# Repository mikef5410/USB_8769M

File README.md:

## USB_8769M 

USB control of Keysight 50GHz SP6T.

Related projects: [my USB Dual SPDT project](https://github.com/mikef5410/USB_SPDT)  and  [the software for these projects](https://github.com/mikef5410/USB_Attenuator_Switch_Stacklight)

# Project setup

The software is included here as a git submodule. After cloning, do a
`git submodule init` followed by `git submodule update --recursive`

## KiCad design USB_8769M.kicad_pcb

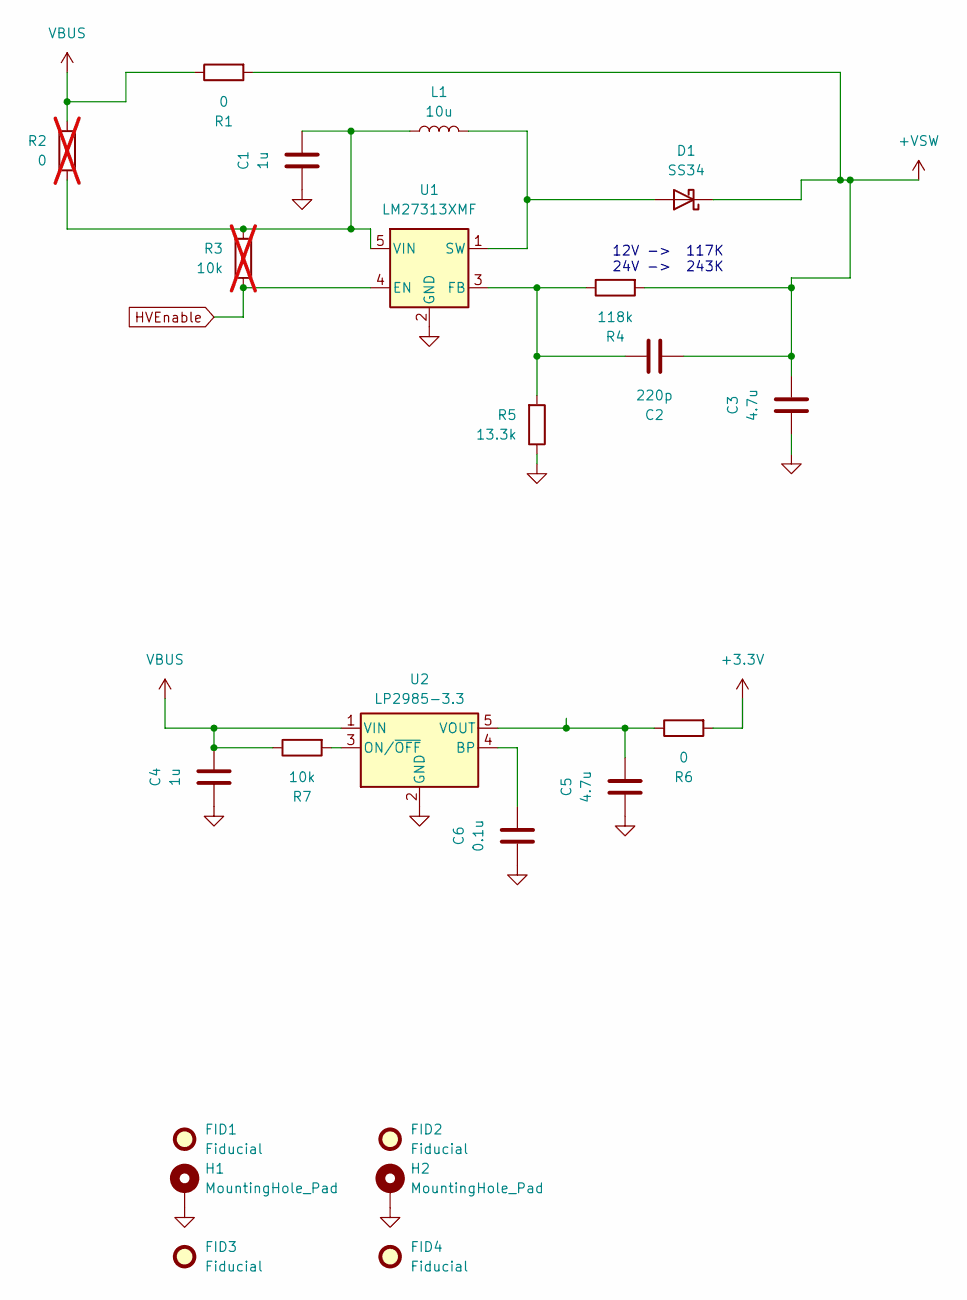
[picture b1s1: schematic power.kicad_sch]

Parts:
C1, C4: 1u; C_0603_1608Metric_Pad1.08x0.95mm_HandSolder; LCSC C15849
C2: 220p; C_0402_1005Metric_Pad0.74x0.62mm_HandSolder; LCSC C1603
C3: 4.7u; C_0805_2012Metric_Pad1.18x1.45mm_HandSolder; LCSC C1779
C5: 4.7u; C_0402_1005Metric_Pad0.74x0.62mm_HandSolder; LCSC C106859
C6: 0.1u; C_0402_1005Metric_Pad0.74x0.62mm_HandSolder; LCSC C5142567
D1: SS34; D_SMA; LCSC C8678
FID1, FID2, FID3, FID4: Fiducial; Fiducial_1mm_Mask3mm
H1, H2: MountingHole_Pad; MountingHole_3.2mm_M3_DIN965_Pad_TopBottom
L1: 10u; L_Changjiang_FNR4030S; LCSC C167879
R1, R6: 0; R_0402_1005Metric_Pad0.72x0.64mm_HandSolder; LCSC C17168
R2: 0; R_0402_1005Metric_Pad0.72x0.64mm_HandSolder; LCSC C17168; not fitted
R3: 10k; R_0402_1005Metric_Pad0.72x0.64mm_HandSolder; LCSC C25744; not fitted
R4: 118k; R_0402_1005Metric_Pad0.72x0.64mm_HandSolder; LCSC C25748
R5: 13.3k; R_0402_1005Metric_Pad0.72x0.64mm_HandSolder; LCSC C122547
R7: 10k; R_0402_1005Metric_Pad0.72x0.64mm_HandSolder; LCSC C25744
U1: LM27313XMF; SOT-23-5; LCSC C341750
U2: LP2985-3.3; SOT-23-5; LCSC C109382

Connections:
+3.3V: R6.2; also elsewhere on the board
+VSW: C2.1, C3.2, D1.1 (K), R1.2, R4.2; also elsewhere on the board
GND: C1.1, C3.1, C4.1, C5.1, C6.1, H1.1, H2.1, R5.1, U1.2 (GND), U2.2 (GND); also elsewhere on the board
HVEnable: R3.1, U1.4 (EN); also elsewhere on the board
unnamed: D1.2 (A), L1.2, U1.1 (SW)
unnamed: C2.2, R4.1, R5.2, U1.3 (FB)
unnamed: C1.2, L1.1, R2.1, R3.2, U1.5 (VIN)
unnamed: C6.2, U2.4 (BP)
unnamed: R7.2, U2.3 (ON/~OFF)
unnamed: C5.2, R6.1, U2.5 (VOUT)
VBUS: C4.2, R1.1, R2.2, R7.1, U2.1 (VIN); also elsewhere on the board

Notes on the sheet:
12V -> 117K 24V -> 243K

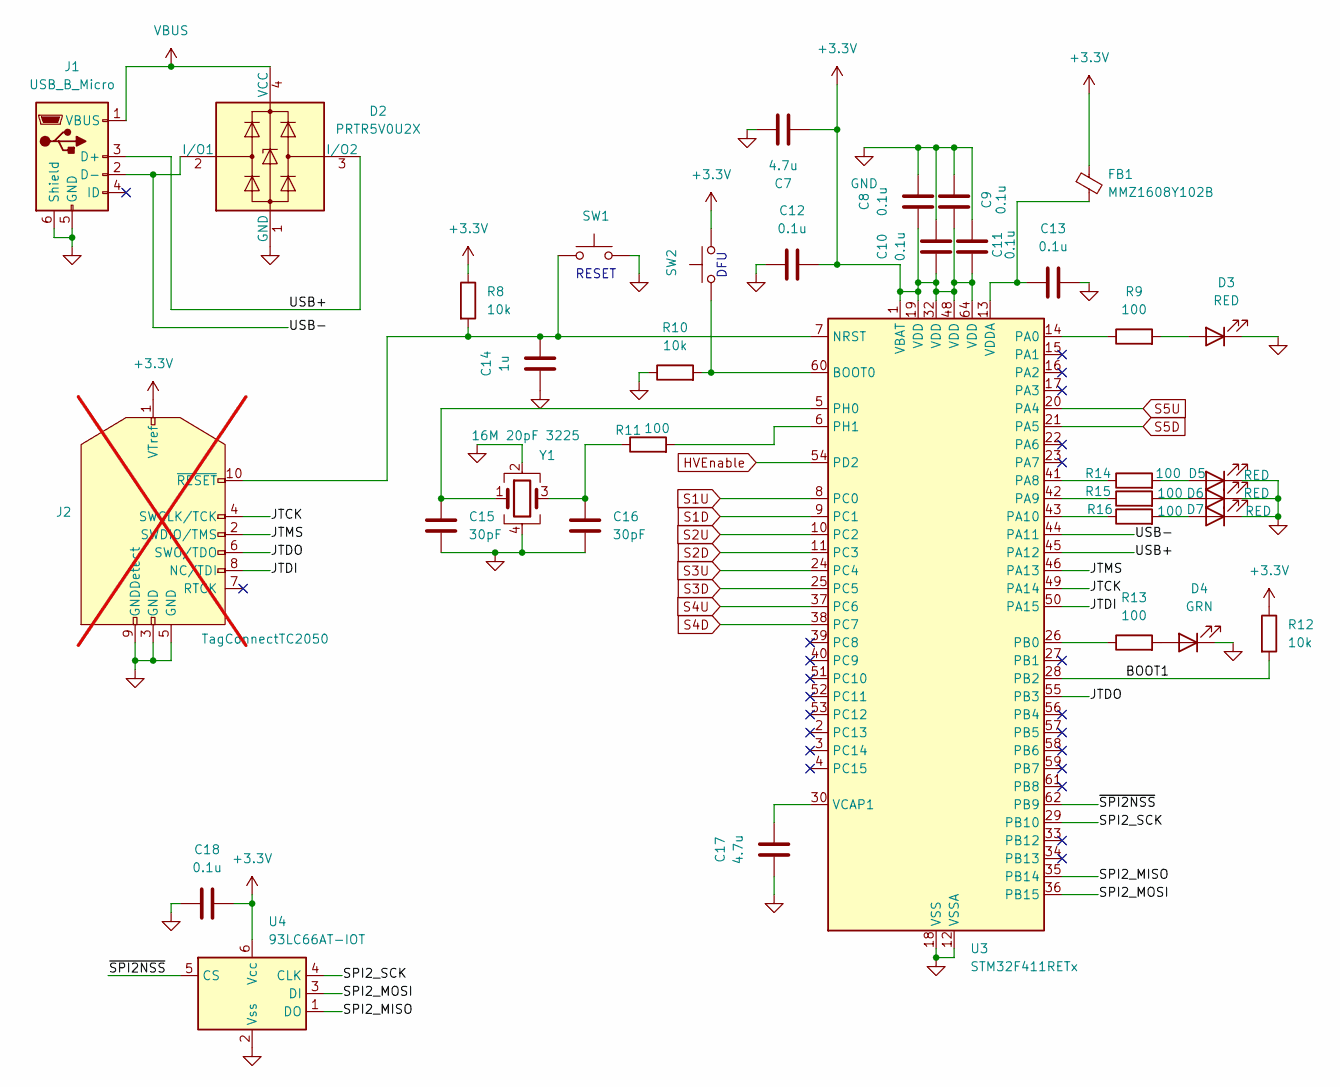
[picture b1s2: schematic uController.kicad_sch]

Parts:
C7, C17: 4.7u; C_0402_1005Metric_Pad0.74x0.62mm_HandSolder; LCSC C106859
C8, C9, C10, C11, C12, C13, C18: 0.1u; C_0402_1005Metric_Pad0.74x0.62mm_HandSolder; LCSC C5142567
C14: 1u; C_0603_1608Metric_Pad1.08x0.95mm_HandSolder; LCSC C15849
C15, C16: 30pF; C_0402_1005Metric_Pad0.74x0.62mm_HandSolder; LCSC C1658
D2: PRTR5V0U2X; SOT-143; LCSC C2827688
D3, D5, D6, D7: RED; LED_0603_1608Metric_Pad1.05x0.95mm_HandSolder; LCSC C84263
D4: GRN; LED_0603_1608Metric_Pad1.05x0.95mm_HandSolder; LCSC C434423
FB1: MMZ1608Y102B; C_0603_1608Metric_Pad1.08x0.95mm_HandSolder; LCSC C114771
J1: USB_B_Micro; USB_Micro-B_Amphenol_10118193-0001LF_Horizontal; LCSC C132562
J2: TagConnectTC2050; Tag-Connect_TC2050-IDC-FP_2x05_P1.27mm_Vertical; not fitted
R8, R10, R12: 10k; R_0402_1005Metric_Pad0.72x0.64mm_HandSolder; LCSC C25744
R9, R11, R13, R14, R15, R16: 100; R_0402_1005Metric_Pad0.72x0.64mm_HandSolder; LCSC C25076
SW1, SW2: SW_Push; SW_Tactile_SPST_NO_Straight_CK_PTS636Sx25SMTRLFS; LCSC C2800965
U3: STM32F411RETx; LQFP-64_10x10mm_P0.5mm; LCSC C94355
U4: 93LC66AT-IOT; SOT-23-6; LCSC C511344
Y1: 16M 20pF 3225; Crystal_SMD_3225-4Pin_3.2x2.5mm_HandSoldering; MPN 7U16000E20UCG; LCSC C524727

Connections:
+3.3V: C7.1, C8.1, C9.2, C10.1, C11.1, C12.2, C18.2, FB1.1, J2.1 (VTref), R8.1, R12.1, SW2.2, U3.1 (VBAT), U3.19 (VDD), U3.32 (VDD), U3.48 (VDD), U3.64 (VDD), U4.6 (Vcc); also elsewhere on the board
/uController/BOOT1: R12.2, U3.28 (PB2)
/uController/JTCK: J2.4 (SWCLK/TCK), U3.49 (PA14)
/uController/JTDI: J2.8 (NC/TDI), U3.50 (PA15)
/uController/JTDO: J2.6 (SWO/TDO), U3.55 (PB3)
/uController/JTMS: J2.2 (SWDIO/TMS), U3.46 (PA13)
/uController/SPI2_MISO: U3.35 (PB14), U4.1 (DO)
/uController/SPI2_MOSI: U3.36 (PB15), U4.3 (DI)
/uController/SPI2_SCK: U3.29 (PB10), U4.4 (CLK)
/uController/USB+: D2.3 (I/O2), J1.3 (D+), U3.45 (PA12)
/uController/USB-: D2.2 (I/O1), J1.2 (D-), U3.44 (PA11)
/uController/~SPI2NSS: U3.62 (PB9), U4.5 (CS)
GND: C7.2, C8.2, C9.1, C10.2, C11.2, C12.1, C13.2, C14.1, C15.2, C16.2, C17.1, C18.1, D2.1 (GND), D3.1 (K), D4.1 (K), D5.1 (K), D6.1 (K), D7.1 (K), J1.5 (GND), J1.6 (Shield), J2.3 (GND), J2.5 (GND), J2.9 (GNDDetect), R10.1, SW1.2, U3.12 (VSSA), U3.18 (VSS), U3.31 (VSS), U3.47 (VSS), U3.63 (VSS), U4.2 (Vss), Y1.2, Y1.4; also elsewhere on the board
HVEnable: U3.54 (PD2); also elsewhere on the board
unnamed: C16.1, R11.1, Y1.3
unnamed: D3.2 (A), R9.2
unnamed: D4.2 (A), R13.2
unnamed: D5.2 (A), R14.2
unnamed: D6.2 (A), R15.2
unnamed: D7.2 (A), R16.2
unnamed: C14.2, J2.10 (~RESET), R8.2, SW1.1, U3.7 (NRST)
unnamed: R10.2, SW2.1, U3.60 (BOOT0)
unnamed: R9.1, U3.14 (PA0)
unnamed: R14.1, U3.41 (PA8)
unnamed: R15.1, U3.42 (PA9)
unnamed: R16.1, U3.43 (PA10)
unnamed: R13.1, U3.26 (PB0)
unnamed: C15.1, U3.5 (PH0), Y1.1
unnamed: R11.2, U3.6 (PH1)
unnamed: C17.2, U3.30 (VCAP1)
unnamed: C13.1, FB1.2, U3.13 (VDDA)
S1D: U3.9 (PC1); also elsewhere on the board
S1U: U3.8 (PC0); also elsewhere on the board
S2D: U3.11 (PC3); also elsewhere on the board
S2U: U3.10 (PC2); also elsewhere on the board
S3D: U3.25 (PC5); also elsewhere on the board
S3U: U3.24 (PC4); also elsewhere on the board
S4D: U3.38 (PC7); also elsewhere on the board
S4U: U3.37 (PC6); also elsewhere on the board
S5D: U3.21 (PA5); also elsewhere on the board
S5U: U3.20 (PA4); also elsewhere on the board
VBUS: D2.4 (VCC), J1.1 (VBUS); also elsewhere on the board

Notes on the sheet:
RESET
DFU

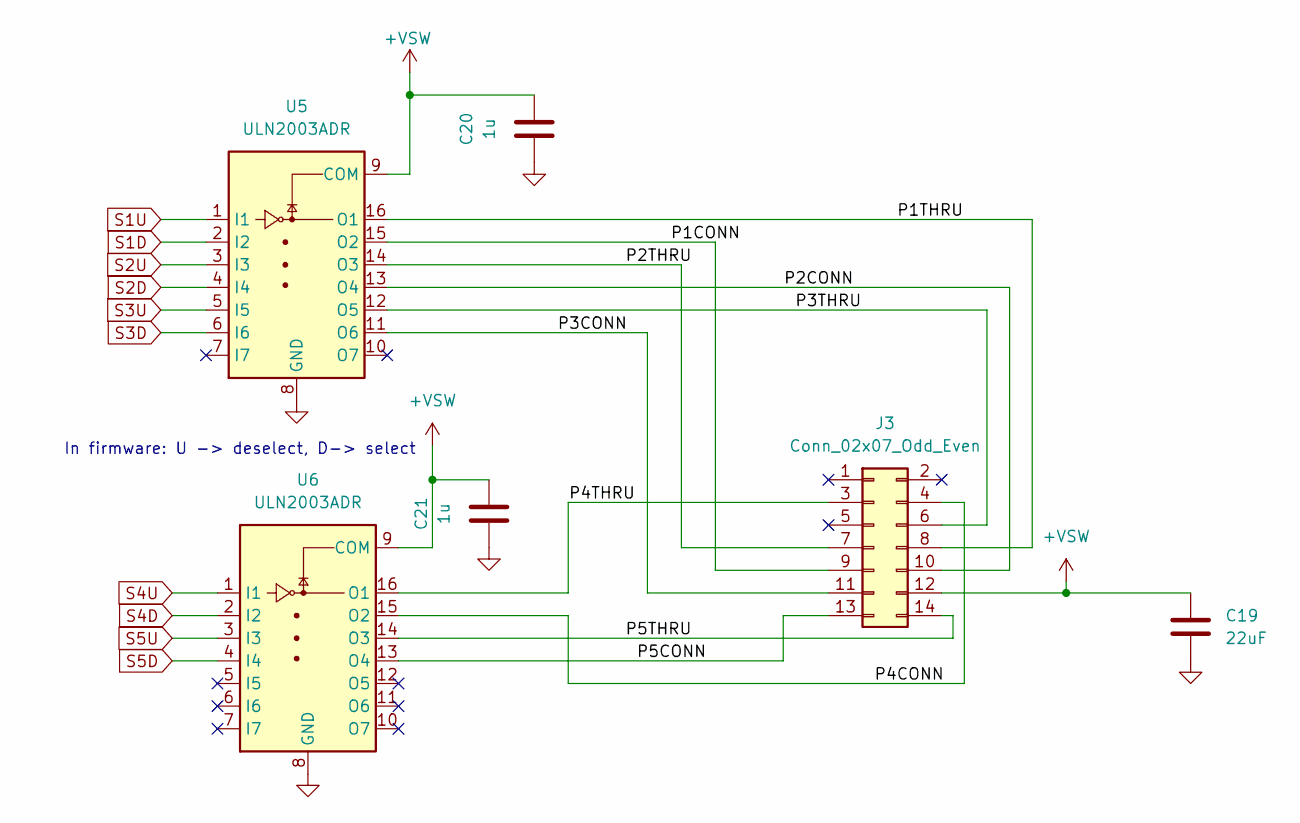
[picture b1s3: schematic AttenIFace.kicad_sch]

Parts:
C19: 22uF; C_1206_3216Metric_Pad1.33x1.80mm_HandSolder; LCSC C12891
C20, C21: 1u; C_0603_1608Metric_Pad1.08x0.95mm_HandSolder; LCSC C15849
J3: Conn_02x07_Odd_Even; IDC-Header_2x07_P2.54mm_Vertical; LCSC C11215
U5, U6: ULN2003ADR; SOIC-16_4.55x10.3mm_P1.27mm; LCSC C7512

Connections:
+VSW: C19.1, C20.2, C21.2, J3.12, U5.9 (COM), U6.9 (COM); also elsewhere on the board
/AttenIFace/P1CONN: J3.9, U5.15 (O2)
/AttenIFace/P1THRU: J3.8, U5.16 (O1)
/AttenIFace/P2CONN: J3.10, U5.13 (O4)
/AttenIFace/P2THRU: J3.7, U5.14 (O3)
/AttenIFace/P3CONN: J3.11, U5.11 (O6)
/AttenIFace/P3THRU: J3.6, U5.12 (O5)
/AttenIFace/P4CONN: J3.4, U6.15 (O2)
/AttenIFace/P4THRU: J3.3, U6.16 (O1)
/AttenIFace/P5CONN: J3.13, U6.13 (O4)
/AttenIFace/P5THRU: J3.14, U6.14 (O3)
GND: C19.2, C20.1, C21.1, U5.8 (GND), U6.8 (GND); also elsewhere on the board
S1D: U5.2 (I2); also elsewhere on the board
S1U: U5.1 (I1); also elsewhere on the board
S2D: U5.4 (I4); also elsewhere on the board
S2U: U5.3 (I3); also elsewhere on the board
S3D: U5.6 (I6); also elsewhere on the board
S3U: U5.5 (I5); also elsewhere on the board
S4D: U6.2 (I2); also elsewhere on the board
S4U: U6.1 (I1); also elsewhere on the board
S5D: U6.4 (I4); also elsewhere on the board
S5U: U6.3 (I3); also elsewhere on the board

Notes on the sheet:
In firmware: U -> deselect, D-> select

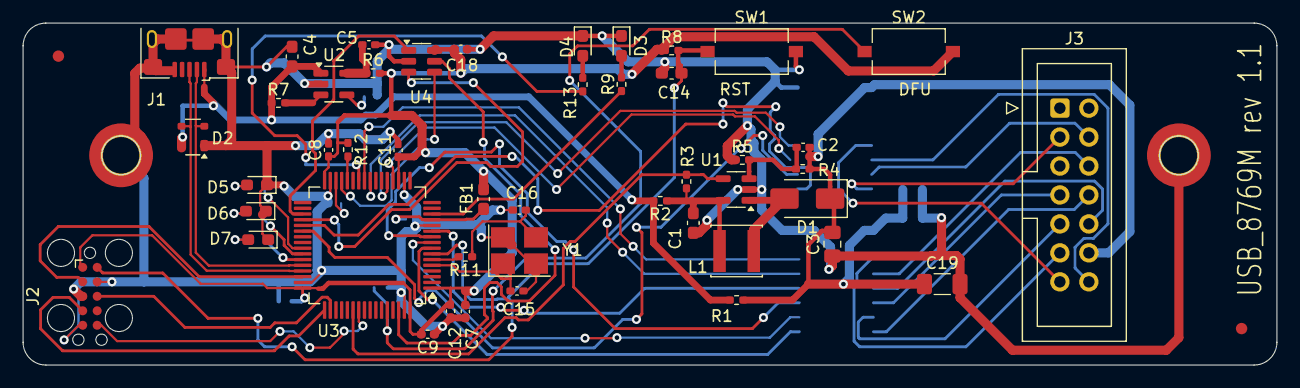
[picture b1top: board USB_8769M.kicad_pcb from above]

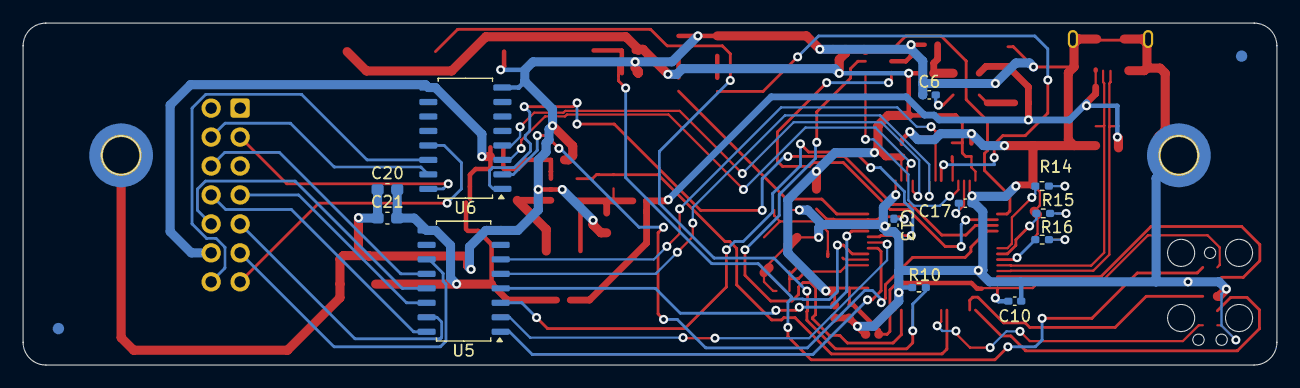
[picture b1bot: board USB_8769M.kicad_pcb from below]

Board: 2 copper layers, 110.0 x 30.0 mm, 64 parts (14 on the bottom side), 59 nets.

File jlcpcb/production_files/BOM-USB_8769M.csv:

Comment,Designator,Footprint,LCSC
LP2985-3.3,U2,SOT-23-5,C109382
Conn_02x07_Odd_Even,J3,IDC-Header_2x07_P2.54mm_Vertical,C11215
MMZ1608Y102B,FB1,C_0603_1608Metric_Pad1.08x0.95mm_HandSolder,C114771
13.3k,R5,R_0402_1005Metric_Pad0.72x0.64mm_HandSolder,C122547
22uF,C19,C_1206_3216Metric_Pad1.33x1.80mm_HandSolder,C12891
USB_B_Micro,J1,USB_Micro-B_Amphenol_10118193-0001LF_Horizontal,C132562
1u,"C1,C14,C20,C21,C4",C_0603_1608Metric_Pad1.08x0.95mm_HandSolder,C15849
220p,C2,C_0402_1005Metric_Pad0.74x0.62mm_HandSolder,C1603
30pF,"C15,C16",C_0402_1005Metric_Pad0.74x0.62mm_HandSolder,C1658
10u,L1,L_Changjiang_FNR4030S,C167879
0,"R1,R6",R_0402_1005Metric_Pad0.72x0.64mm_HandSolder,C17168
4.7u,"C17,C3,C5,C7",C_0402_1005Metric_Pad0.74x0.62mm_HandSolder,C1779
100,"R11,R13,R14,R15,R16,R9",R_0402_1005Metric_Pad0.72x0.64mm_HandSolder,C25076
10k,"R10,R12,R7,R8",R_0402_1005Metric_Pad0.72x0.64mm_HandSolder,C25744
118k,R4,R_0402_1005Metric_Pad0.72x0.64mm_HandSolder,C25748
SW_Push,"SW1,SW2",SW_Tactile_SPST_NO_Straight_CK_PTS636Sx25SMTRLFS,C2800965
PRTR5V0U2X,D2,SOT-143,C2827688
LM27313XMF,U1,SOT-23-5,C341750
GRN,D4,LED_0603_1608Metric_Pad1.05x0.95mm_HandSolder,C434423
93LC66AT-IOT,U4,SOT-23-6,C511344
0.1u,"C10,C11,C12,C13,C18,C6,C8,C9",C_0402_1005Metric_Pad0.74x0.62mm_HandSolder,C5142567
16M 20pF 3225,Y1,Crystal_SMD_3225-4Pin_3.2x2.5mm_HandSoldering,C524727
ULN2003ADR,"U5,U6",SOIC-16_4.55x10.3mm_P1.27mm,C7512
RED,"D3,D5,D6,D7",LED_0603_1608Metric_Pad1.05x0.95mm_HandSolder,C84263
SS34,D1,D_SMA,C8678
STM32F411RETx,U3,LQFP-64_10x10mm_P0.5mm,C94355

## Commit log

2024-05-20 Initial checkin
2024-05-21 C3,5,7,17 had LCSC changed to rev 1.1
2024-05-22 Update JLCPCB files. Part rotations will be incorrect, as I correct them on the website.
2024-05-27 Add MIT License
2024-06-06 Wrong LCSC part number for 3.3V regulator. BOOT1 needs to be held LOW not HIGH.
2024-06-06 Add firmware as a submodule and README.md
2024-07-19 Add step model for 8769M
